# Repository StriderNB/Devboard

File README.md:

# RP2040 Devboard
Week 5 project of Hack club Half Life

# Details
A devboard Based off of the Raspberry Pi Pico using the RP2040 Microcontroller.

28 GPIO pins

Red power led on the top right and a yellow green test led on the bottom right GPIO 25

Bottom button is reset, top button is boot

Don't have a table of the pinouts yet but they are available in the images below.
# BOM
*Note these are bulk quantities not exact

| Item | Qty | Supplier | Cost/item | Total Cost | Link |
| :--- | :---: | :--- | :---: | :---: | :--- |
| 1uF capacitor | 50 | LCSC | $0.01 | $0.50 | [Link](https://www.lcsc.com/product-detail/C29266.html?spm=wm.gwc.xh.0.cbm___wm.fly.ssl.gwc&lcsc_vid=TgdYAQdQRwdeUABeRQdeVFRSEgJdX1VWFFVZUVEFRAMxVlNfQ1BXVlNRT1NZXzsOAxUeFF5JWBYZEEoKFBINSQcJGk4dAgUUFAk%3D) |
| 0.1uF capacitor | 100 | LCSC | $0.0032 | $0.32 | [Link](https://www.lcsc.com/product-detail/C1525.html?spm=wm.gwc.xh.1.cbm___wm.fly.ssl.gwc&lcsc_vid=TgdYAQdQRwdeUABeRQdeVFRSEgJdX1VWFFVZUVEFRAMxVlNfQ1BXVlNRT1NZXzsOAxUeFF5JWBYZEEoKFBINSQcJGk4dAgUUFAk%3D) |
| 10uF capacitor | 20 | LCSC | $0.0205 | $0.41 | [Link](https://www.lcsc.com/product-detail/C19702.html?spm=wm.gwc.xh.2.cbm___wm.fly.ssl.gwc&lcsc_vid=TgdYAQdQRwdeUABeRQdeVFRSEgJdX1VWFFVZUVEFRAMxVlNfQ1BXVlNRT1NZXzsOAxUeFF5JWBYZEEoKFBINSQcJGk4dAgUUFAk%3D) |
| 33pF capacitor | 100 | LCSC | $0.002 | $0.2 | [Link](https://www.lcsc.com/product-detail/C107005.html?spm=wm.gwc.xh.3.cbm___wm.fly.ssl.gwc&lcsc_vid=TgdYAQdQRwdeUABeRQdeVFRSEgJdX1VWFFVZUVEFRAMxVlNfQ1BXVlNRT1NZXzsOAxUeFF5JWBYZEEoKFBINSQcJGk4dAgUUFAk%3D) |
| USB-C Receptacle 12PIN | 5 | LCSC | $0.1736 | $0.87 | [Link](https://www.lcsc.com/product-detail/C165948.html?spm=wm.gwc.xh.11.cbm___wm.fly.ssl.gwc&lcsc_vid=TgdYAQdQRwdeUABeRQdeVFRSEgJdX1VWFFVZUVEFRAMxVlNfQ1BXVlNRT1NZXzsOAxUeFF5JWBYZEEoKFBINSQcJGk4dAgUUFAk%3D) |
| Conn_01x20 | 5 | LCSC | $0.0856 | $0.43 | [Link](https://www.lcsc.com/product-detail/C42431804.html?spm=wm.gwc.xh.4.cbm___wm.fly.ssl.gwc&lcsc_vid=TgdYAQdQRwdeUABeRQdeVFRSEgJdX1VWFFVZUVEFRAMxVlNfQ1BXVlNRT1NZXzsOAxUeFF5JWBYZEEoKFBINSQcJGk4dAgUUFAk%3D) |
| 5.1k resistor | 100 | LCSC | $0.0011 | $0.11 | [Link](https://www.lcsc.com/product-detail/C2906874.html?spm=wm.gwc.xh.6.cbm___wm.fly.ssl.gwc&lcsc_vid=TgdYAQdQRwdeUABeRQdeVFRSEgJdX1VWFFVZUVEFRAMxVlNfQ1BXVlNRT1NZXzsOAxUeFF5JWBYZEEoKFBINSQcJGk4dAgUUFAk%3D) |
| 27 ohm resistor | 100 | LCSC | $0.0013 | $0.13 | [Link](https://www.lcsc.com/product-detail/C25100.html?spm=wm.gwc.xh.7.cbm___wm.fly.ssl.gwc&lcsc_vid=TgdYAQdQRwdeUABeRQdeVFRSEgJdX1VWFFVZUVEFRAMxVlNfQ1BXVlNRT1NZXzsOAxUeFF5JWBYZEEoKFBINSQcJGk4dAgUUFAk%3D) |
| 1k resistor | 100 | LCSC | $0.0026 | $0.26 | [Link](https://www.lcsc.com/product-detail/C106235.html?spm=wm.gwc.xh.5.cbm___wm.fly.ssl.gwc&lcsc_vid=TgdYAQdQRwdeUABeRQdeVFRSEgJdX1VWFFVZUVEFRAMxVlNfQ1BXVlNRT1NZXzsOAxUeFF5JWBYZEEoKFBINSQcJGk4dAgUUFAk%3D) |
| 10k resistor| 100 | LCSC | $0.0017 | $0.17 | [Link](https://www.lcsc.com/product-detail/C60490.html?spm=wm.gwc.xh.8.cbm___wm.fly.ssl.gwc&lcsc_vid=TgdYAQdQRwdeUABeRQdeVFRSEgJdX1VWFFVZUVEFRAMxVlNfQ1BXVlNRT1NZXzsOAxUeFF5JWBYZEEoKFBINSQcJGk4dAgUUFAk%3D) |
| SPST switch | 20 | LCSC | $0.0507 | $1.01 | [Link](https://www.lcsc.com/product-detail/C720477.html?spm=wm.gwc.xh.9.cbm___wm.fly.ssl.gwc&lcsc_vid=TgdYAQdQRwdeUABeRQdeVFRSEgJdX1VWFFVZUVEFRAMxVlNfQ1BXVlNRT1NZXzsOAxUeFF5JWBYZEEoKFBINSQcJGk4dAgUUFAk%3D) |
| RP2040 Microcontroller | 3 | LCSC | $1.0969 | $3.29 | [Link](https://www.lcsc.com/product-detail/C2040.html?spm=wm.gwc.xh.10.cbm___wm.fly.ssl.gwc&lcsc_vid=TgdYAQdQRwdeUABeRQdeVFRSEgJdX1VWFFVZUVEFRAMxVlNfQ1BXVlNRT1NZXzsOAxUeFF5JWBYZEEoKFBINSQcJGk4dAgUUFAk%3D) |
| MCP1700x-330xxTT voltage LDO | 10 | LCSC | $0.0759 | $0.76 | [Link](https://www.lcsc.com/product-detail/C42417262.html?spm=wm.gwc.xh.14.cbm___wm.fly.ssl.gwc&lcsc_vid=TgdYAQdQRwdeUABeRQdeVFRSEgJdX1VWFFVZUVEFRAMxVlNfQ1BXVlNRT1NZXzsOAxUeFF5JWBYZEEoKFBINSQcJGk4dAgUUFAk%3D) |
| W25Q16JVUXIQ Flash memory | 4 | LCSC | $1.5912 | $6.36 | [Link](https://www.lcsc.com/product-detail/C2843335.html?spm=wm.gwc.xh.13.cbm___wm.fly.ssl.gwc&lcsc_vid=TgdYAQdQRwdeUABeRQdeVFRSEgJdX1VWFFVZUVEFRAMxVlNfQ1BXVlNRT1NZXzsOAxUeFF5JWBYZEEoKFBINSQcJGk4dAgUUFAk%3D) |
| 12mhz X322512MSB4SI crystal ocillator | 5 | LCSC | $0.917 | $0.48 | [Link](https://www.lcsc.com/product-detail/C9002.html?spm=wm.gwc.xh.12.cbm___wm.fly.ssl.gwc&lcsc_vid=TgdYAQdQRwdeUABeRQdeVFRSEgJdX1VWFFVZUVEFRAMxVlNfQ1BXVlNRT1NZXzsOAxUeFF5JWBYZEEoKFBINSQcJGk4dAgUUFAk%3D) |
| Red Led | 100 | LCSC | $0.59 | $0.0059 | [Link](https://www.lcsc.com/product-detail/C19171390.html?spm=wm.gwc.xh.15.cbm___wm.sxq.ssl.gwc&lcsc_vid=FQdbAlNQRVZfUl1RQ1UKUVUFE1cKU1QAQVAMBVMAR1UxVlNfQ1VdU1dRRFhdUzsOAxUeFF5JWBYZEEoKFBINSQcJGk4dAgUUFAk%3D) |
| Yellow Green Led | 20 | LCSC | $0.0186 | $0.37 | [Link](https://www.lcsc.com/product-detail/C125094.html?spm=wm.gwc.xh.16.cbm___wm.sxq.ssl.gwc&lcsc_vid=FQdbAlNQRVZfUl1RQ1UKUVUFE1cKU1QAQVAMBVMAR1UxVlNfQ1VdU1dRRFhdUzsOAxUeFF5JWBYZEEoKFBINSQcJGk4dAgUUFAk%3D) |
| PCB | 5 | JLCPCB | | $4.10 | [Link](https://jlcpcb.com/) |
| Estimated total shipping | 1 | | | $15.37 | |
| TOTAL  |  | | | $34.40 | |
# Images

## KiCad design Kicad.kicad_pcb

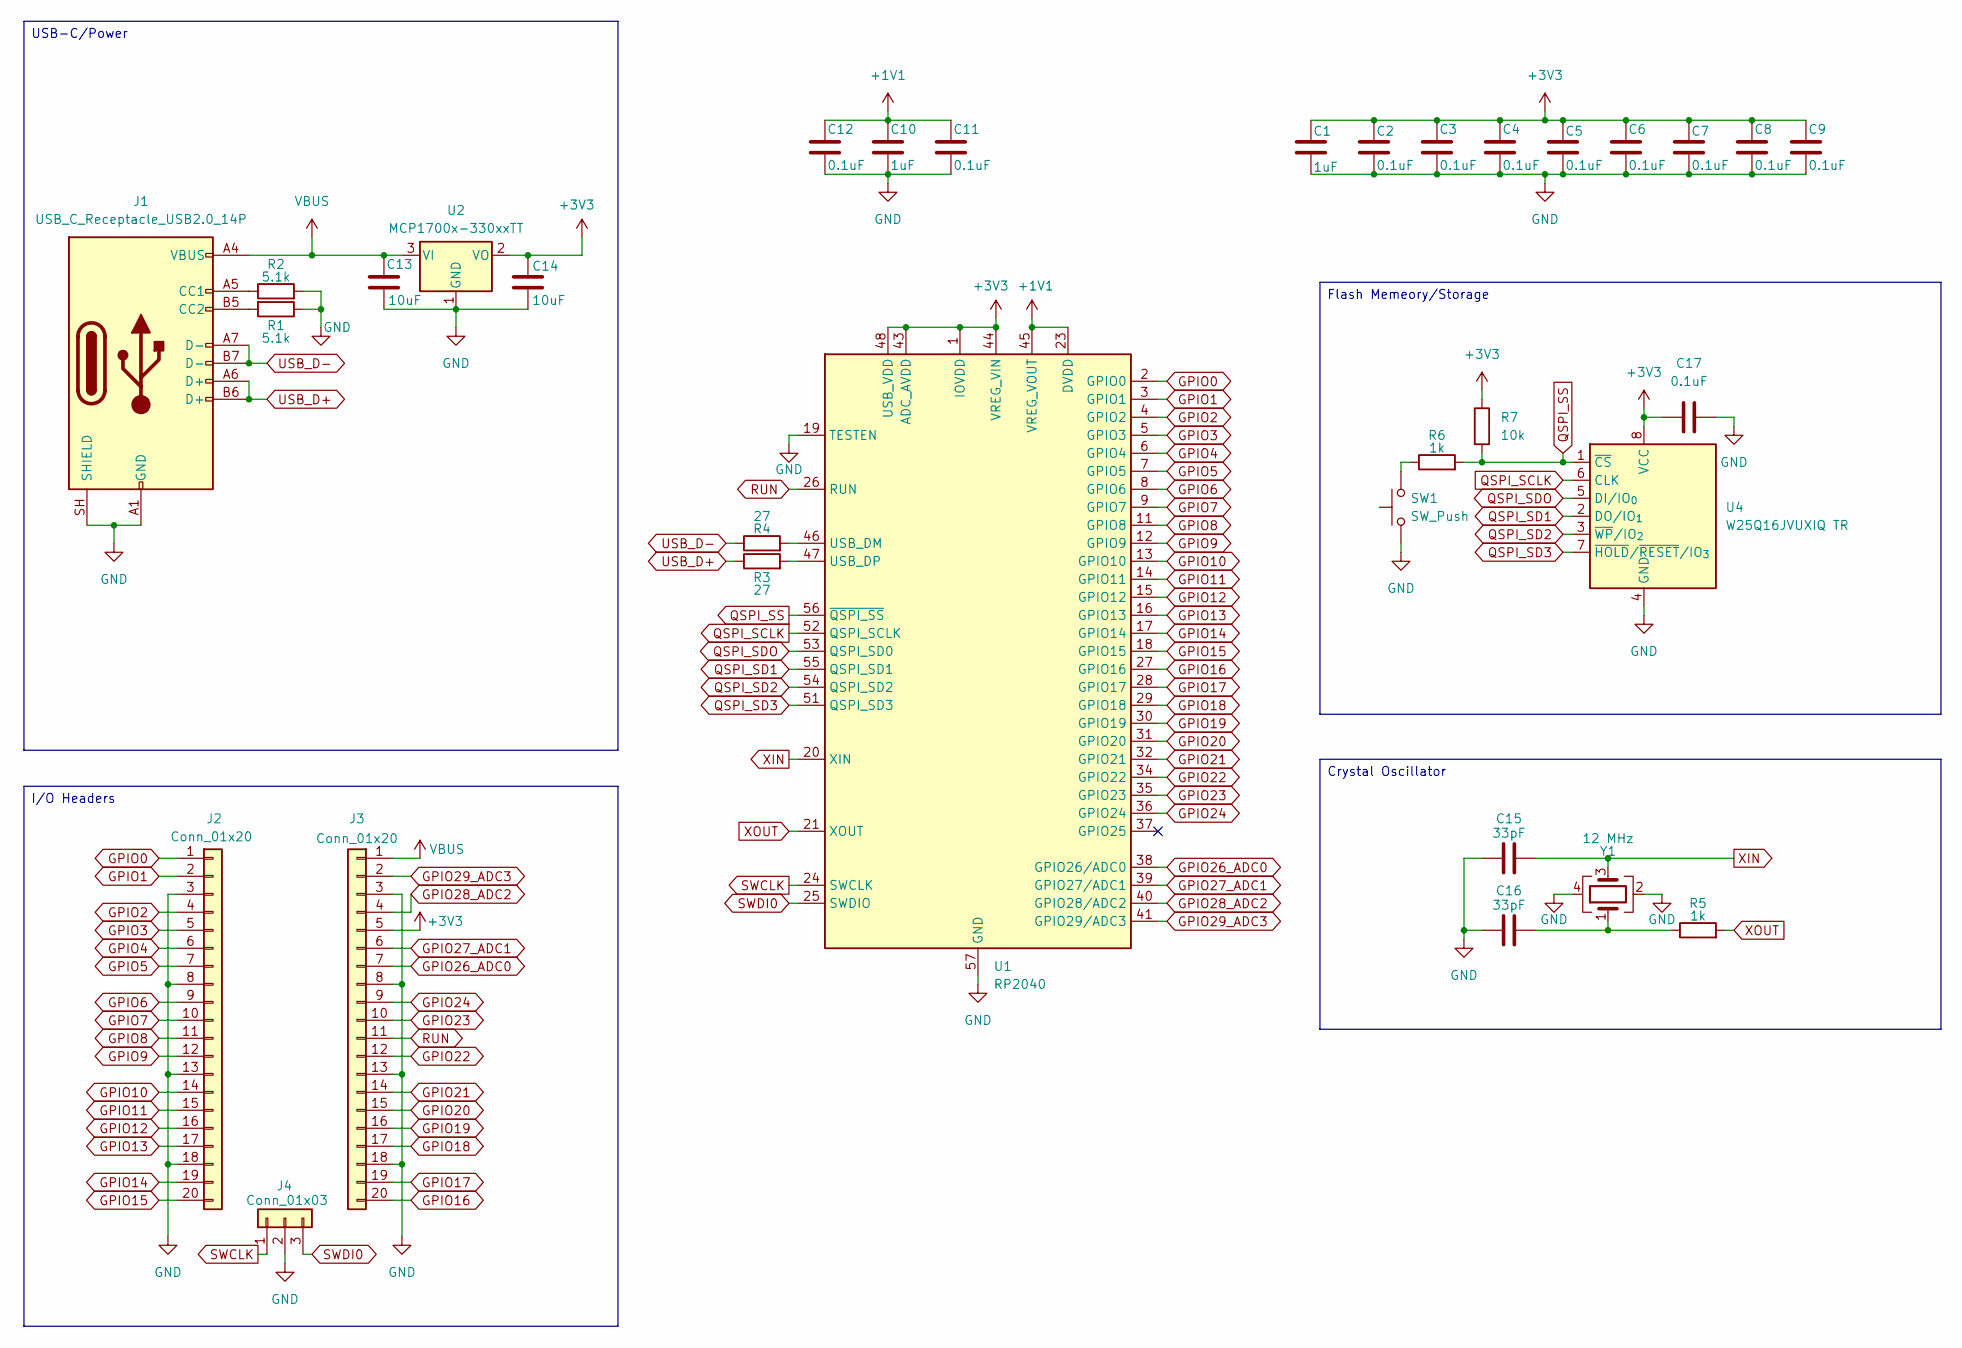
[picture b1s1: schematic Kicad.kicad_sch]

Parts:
C1, C10: 1uF; C_0402_1005Metric
C2, C3, C4, C5, C6, C7, C8, C9, C11, C12, C17: 0.1uF; C_0402_1005Metric
C13, C14: 10uF; C_0603_1608Metric
C15, C16: 33pF; C_0402_1005Metric
J1: USB_C_Receptacle_USB2.0_14P; USB_C_Receptacle_HRO_TYPE-C-31-M-12
J2, J3: Conn_01x20; PinHeader_1x20_P2.54mm_Vertical
J4: Conn_01x03; PinHeader_1x03_P2.54mm_Vertical
R1, R2: 5.1k; C_0402_1005Metric
R3, R4: 27; C_0402_1005Metric
R5, R6: 1k; C_0402_1005Metric
R7: 10k; C_0402_1005Metric
SW1: SW_Push; SW_Push_SPST_NO_Alps_SKRK
U1: RP2040; QFN-56-1EP_7x7mm_P0.4mm_EP3.2x3.2mm
U2: MCP1700x-330xxTT; SOT-23
U4: W25Q16JVUXIQ TR; Winbond_USON-8-1EP_3x2mm_P0.5mm_EP0.2x1.6mm
Y1: 12 MHz; Crystal_SMD_3225-4Pin_3.2x2.5mm

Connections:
+1V1: C10.1, C11.1, C12.1, U1.23 (DVDD), U1.45 (VREG_VOUT), U1.50 (DVDD)
+3V3: C1.1, C2.1, C3.1, C4.1, C5.1, C6.1, C7.1, C8.1, C9.1, C14.1, C17.1, J3.5, R7.1, U1.1 (IOVDD), U1.10 (IOVDD), U1.22 (IOVDD), U1.33 (IOVDD), U1.42 (IOVDD), U1.43 (ADC_AVDD), U1.44 (VREG_VIN), U1.48 (USB_VDD), U1.49 (IOVDD), U2.2 (VO), U4.8 (VCC)
GND: C1.2, C2.2, C3.2, C4.2, C5.2, C6.2, C7.2, C8.2, C9.2, C10.2, C11.2, C12.2, C13.2, C14.2, C15.1, C16.1, C17.2, J1.A1 (GND), J1.A12 (GND), J1.B1 (GND), J1.B12 (GND), J1.SH (SHIELD), J2.3, J2.8, J2.13, J2.18, J3.3, J3.8, J3.13, J3.18, J4.2, R1.1, R2.2, SW1.1, U1.19 (TESTEN), U1.57 (GND), U2.1 (GND), U4.4 (GND), Y1.2 (G), Y1.4 (G)
GPIO0: J2.1, U1.2 (GPIO0)
GPIO1: J2.2, U1.3 (GPIO1)
GPIO2: J2.4, U1.4 (GPIO2)
GPIO3: J2.5, U1.5 (GPIO3)
GPIO4: J2.6, U1.6 (GPIO4)
GPIO5: J2.7, U1.7 (GPIO5)
GPIO6: J2.9, U1.8 (GPIO6)
GPIO7: J2.10, U1.9 (GPIO7)
GPIO8: J2.11, U1.11 (GPIO8)
GPIO9: J2.12, U1.12 (GPIO9)
GPIO10: J2.14, U1.13 (GPIO10)
GPIO11: J2.15, U1.14 (GPIO11)
GPIO12: J2.16, U1.15 (GPIO12)
GPIO13: J2.17, U1.16 (GPIO13)
GPIO14: J2.19, U1.17 (GPIO14)
GPIO15: J2.20, U1.18 (GPIO15)
GPIO16: J3.20, U1.27 (GPIO16)
GPIO17: J3.19, U1.28 (GPIO17)
GPIO18: J3.17, U1.29 (GPIO18)
GPIO19: J3.16, U1.30 (GPIO19)
GPIO20: J3.15, U1.31 (GPIO20)
GPIO21: J3.14, U1.32 (GPIO21)
GPIO22: J3.12, U1.34 (GPIO22)
GPIO23: J3.10, U1.35 (GPIO23)
GPIO24: J3.9, U1.36 (GPIO24)
GPIO26_ADC0: J3.7, U1.38 (GPIO26/ADC0)
GPIO27_ADC1: J3.6, U1.39 (GPIO27/ADC1)
GPIO28_ADC2: J3.4, U1.40 (GPIO28/ADC2)
GPIO29_ADC3: J3.2, U1.41 (GPIO29/ADC3)
unnamed: C16.2, R5.1, Y1.1
unnamed: J1.A5 (CC1), R2.1
unnamed: J1.B5 (CC2), R1.2
unnamed: R6.1, SW1.2
unnamed: R4.2, U1.46 (USB_DM)
unnamed: R3.2, U1.47 (USB_DP)
QSPI_SCLK: U1.52 (QSPI_SCLK), U4.6 (CLK)
QSPI_SD1: U1.55 (QSPI_SD1), U4.2 (DO/IO_{1})
QSPI_SD2: U1.54 (QSPI_SD2), U4.3 (~WP/IO_{2})
QSPI_SD3: U1.51 (QSPI_SD3), U4.7 (~HOLD/~RESET/IO_{3})
QSPI_SDO: U1.53 (QSPI_SD0), U4.5 (DI/IO_{0})
QSPI_SS: R6.2, R7.2, U1.56 (~QSPI_SS), U4.1 (~CS)
RUN: J3.11, U1.26 (RUN)
SWCLK: J4.1, U1.24 (SWCLK)
SWDI0: J4.3, U1.25 (SWDIO)
USB_D+: J1.A6 (D+), J1.B6 (D+), R3.1
USB_D-: J1.A7 (D-), J1.B7 (D-), R4.1
VBUS: C13.1, J1.A4 (VBUS), J1.A9 (VBUS), J1.B4 (VBUS), J1.B9 (VBUS), J3.1, U2.3 (VI)
XIN: C15.2, U1.20 (XIN), Y1.3
XOUT: R5.2, U1.21 (XOUT)

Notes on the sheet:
Crystal Oscillator
Flash Memeory/Storage
I/O Headers
USB-C/Power

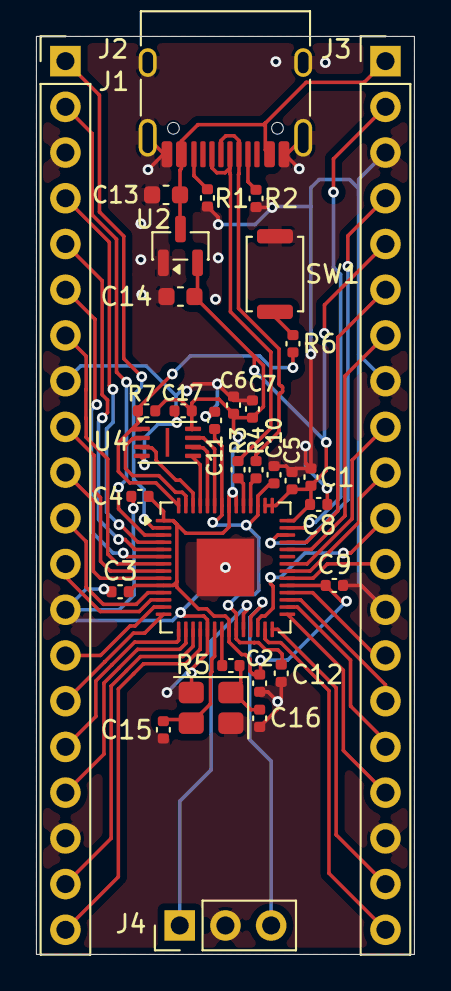
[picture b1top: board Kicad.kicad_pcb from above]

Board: 2 copper layers, 21.0 x 51.0 mm, 33 parts (0 on the bottom side), 52 nets.

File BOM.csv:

Item,Qty,Supplier,Cost/item,Total Cost,link
1uF,2,,$0.00,$0.00,
0.1uF,11,,$0.00,$0.00,
10uF,2,,$0.00,$0.00,
33pF,2,,$0.00,$0.00,
USB_C_Receptacle_USB2.0_14P,1,,$0.00,$0.00,
Conn_01x20,2,,$0.00,$0.00,
Conn_01x03,1,,$0.00,$0.00,
5.1k,2,,$0.00,$0.00,
27,2,,$0.00,$0.00,
1k,2,,$0.00,$0.00,
10k,1,,$0.00,$0.00,
SW_Push,1,,$0.00,$0.00,
RP2040,1,,$0.00,$0.00,
MCP1700x-330xxTT,1,,$0.00,$0.00,
W25Q16JVUXIQ TR,1,,$0.00,$0.00,
12 MHz,1,,$0.00,$0.00,
Estimated total shipping,1,,,$0.00,
